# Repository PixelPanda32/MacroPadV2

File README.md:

# PixelPadV2
## MacroPad made for HackClub hackpad
This is V2 of the hack pad v1 can be accessed here https://github.com/PixelPanda32/MacroPad <br>
4 buttons, 2 knobs and a  oled SCREEEN

## Stuff you could do with it
- volume control, funny little pictures on the screen, button things (keybinds what not )

## CAD Model

Would like to add more **fancy** but couldnt thinkkk of what to add. The box also prototype will change when i have the actual pcb cus i have 3d printers that are accessible so i can print it out and edit it and what not.

## PCB 
I removed two of the buttons in place of another knob.(knobs are cooler and  *twisty*)<br>

Prettyy cool looking Right? made in Kicad snuck a couple qoutes in there. removed the diodes and matrix for simplicity <br>

## FIRMWARE

ive got a kmk firmware which should work but you never know will get it working when i have all the componenets tho and im pretty sure the KMK firmware doesnt need to be complied to anything <br> 

## BOM
4x Some kind of a keycap. <br>
4x MX style switches<br>
3x 1N4148 DO-35 Diodes.<br>
5x SK6812MINI-E<br>
1x 0.91" 128x32 OLED Display<br>
2x EC11 Rotary Encoder<br>
1x XIAO RP2040<br>
1x Case (2 printed parts)<br>

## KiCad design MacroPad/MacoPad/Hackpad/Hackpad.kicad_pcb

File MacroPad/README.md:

# PixelPad
## MacroPad made for HackClub hackpad
4 buttons, 2 knobs and a  oled SCREEEN

## Stuff you could do with it
- volume control, funny little pictures on the screen, button things (keybinds what not )

## CAD Model

Would like to add more **fancy** but couldnt thinkkk of what to add

## PCB 
I removed two of the buttons in place of another knob.(knobs are cooler and  *twisty*)<br>

Prettyy cool looking Right? made in Kicad snuck a couple qoutes in there<br>

## BOM
4x Some kind of a keycap. <br>
4x MX style switches<br>
3x 1N4148 DO-35 Diodes.<br>
5x SK6812MINI-E<br>
1x 0.91" 128x32 OLED Display<br>
2x EC11 Rotary Encoder<br>
1x XIAO RP2040<br>
1x Case (2 printed parts)<br>

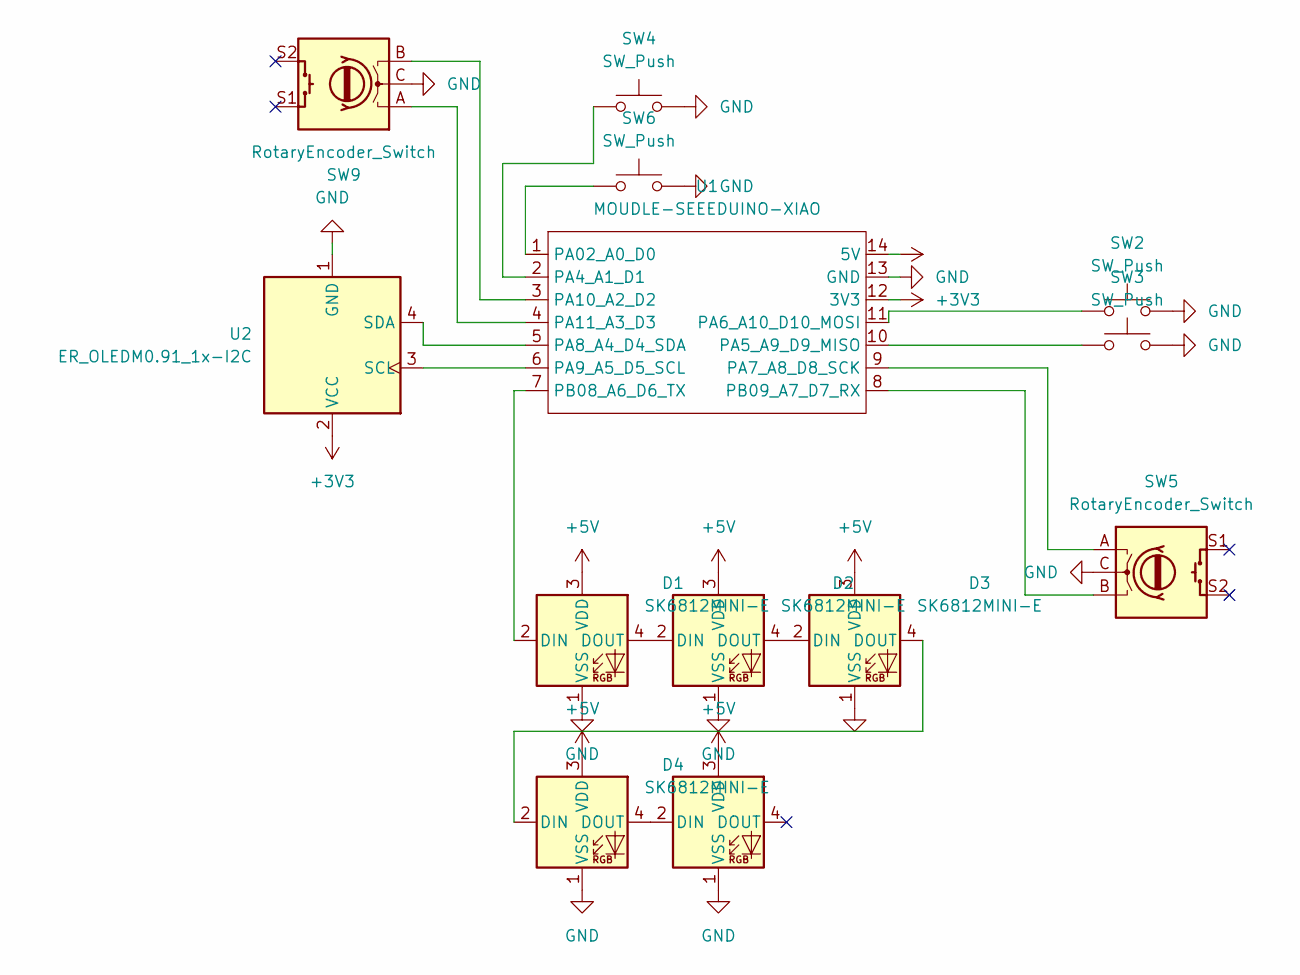
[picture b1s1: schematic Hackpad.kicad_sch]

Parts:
D1, D2, D3, D4, D5: SK6812MINI-E; LED_SK6812MINI-E_3.2x2.8mm_P1.5mm_ReverseMount
SW2, SW3, SW4, SW6: SW_Push; SW_Cherry_MX_1.00u_PCB
SW5: RotaryEncoder_Switch; RotaryEncoder_Alps_EC12E-Switch_Vertical_H20mm
SW9: RotaryEncoder_Switch; RotaryEncoder_Alps_EC11E_Vertical_H20mm
U1: MOUDLE-SEEEDUINO-XIAO; XIAO-Generic-Hybrid-14P-2.54-21X17.8MM
U2: ER_OLEDM0.91_1x-I2C

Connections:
+3V3: U1.12 (3V3), U2.2 (VCC)
+5V: D1.3 (VDD), D2.3 (VDD), D3.3 (VDD), D4.3 (VDD), D5.3 (VDD), U1.14 (5V)
GND: D1.1 (VSS), D2.1 (VSS), D3.1 (VSS), D4.1 (VSS), D5.1 (VSS), SW2.2, SW3.2, SW4.2, SW5.C, SW6.2, SW9.C, U1.13 (GND), U2.1 (GND)
unnamed: D1.2 (DIN), U1.7 (PB08_A6_D6_TX)
unnamed: D1.4 (DOUT), D2.2 (DIN)
unnamed: D2.4 (DOUT), D3.2 (DIN)
unnamed: D3.4 (DOUT), D4.2 (DIN)
unnamed: D4.4 (DOUT), D5.2 (DIN)
unnamed: SW6.1, U1.1 (PA02_A0_D0)
unnamed: SW4.1, U1.2 (PA4_A1_D1)
unnamed: SW3.1, U1.10 (PA5_A9_D9_MISO)
unnamed: SW2.1, U1.11 (PA6_A10_D10_MOSI)
unnamed: SW5.A, U1.9 (PA7_A8_D8_SCK)
unnamed: U1.5 (PA8_A4_D4_SDA), U2.4 (SDA)
unnamed: U1.6 (PA9_A5_D5_SCL), U2.3 (SCL)
unnamed: SW9.B, U1.3 (PA10_A2_D2)
unnamed: SW9.A, U1.4 (PA11_A3_D3)
unnamed: SW5.B, U1.8 (PB09_A7_D7_RX)

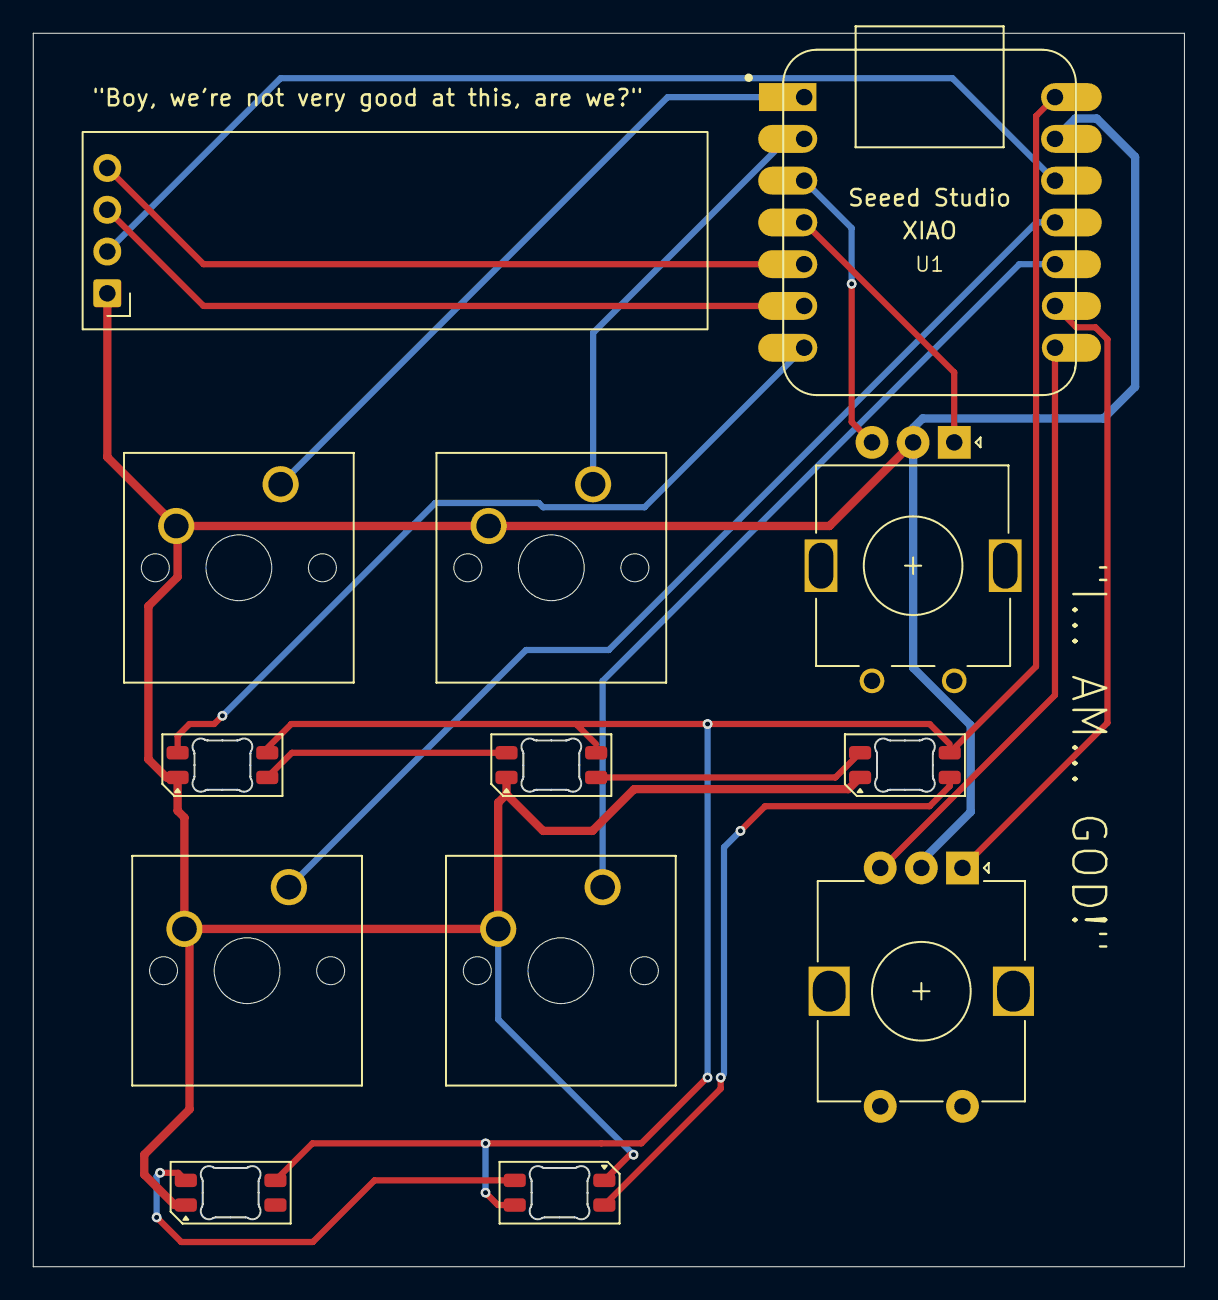
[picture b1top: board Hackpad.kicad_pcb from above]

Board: 2 copper layers, 70.0 x 75.0 mm, 13 parts (0 on the bottom side), 18 nets.
